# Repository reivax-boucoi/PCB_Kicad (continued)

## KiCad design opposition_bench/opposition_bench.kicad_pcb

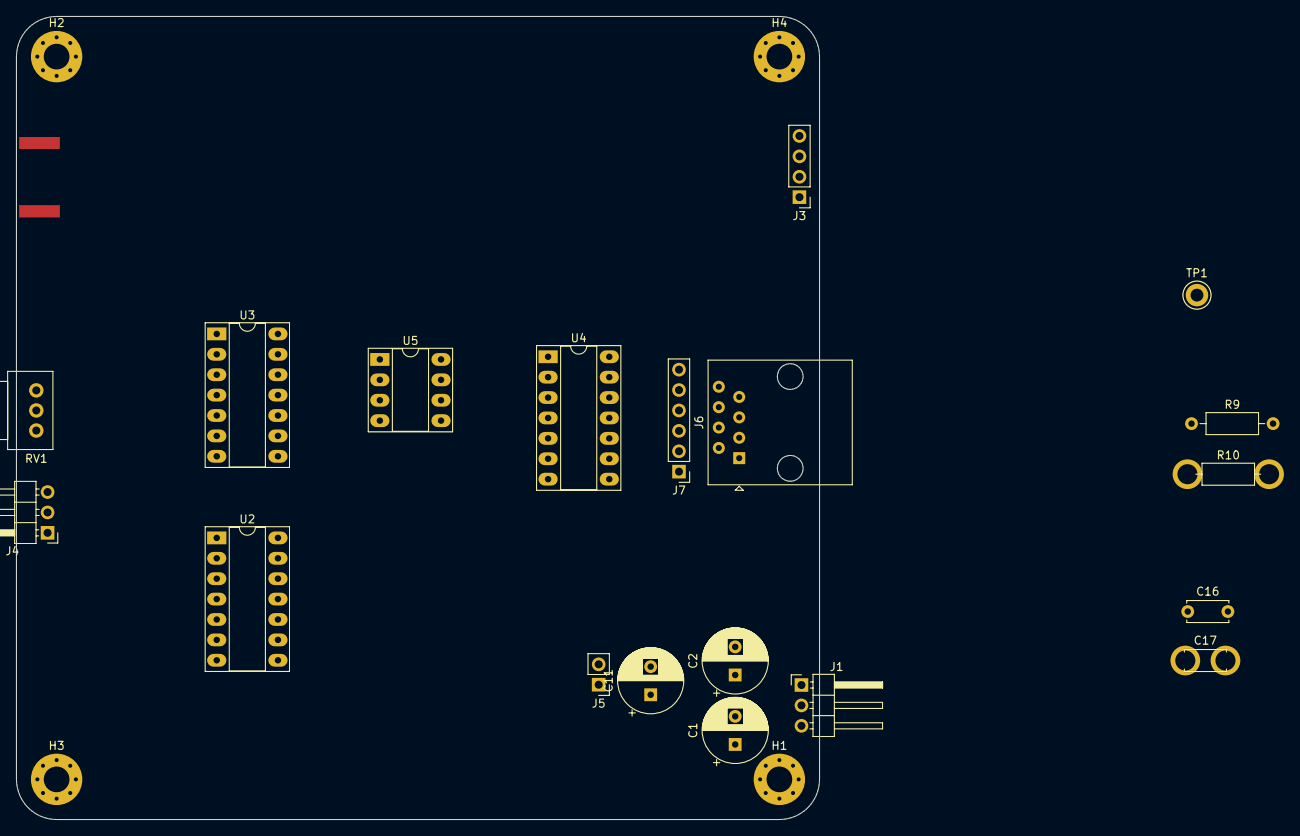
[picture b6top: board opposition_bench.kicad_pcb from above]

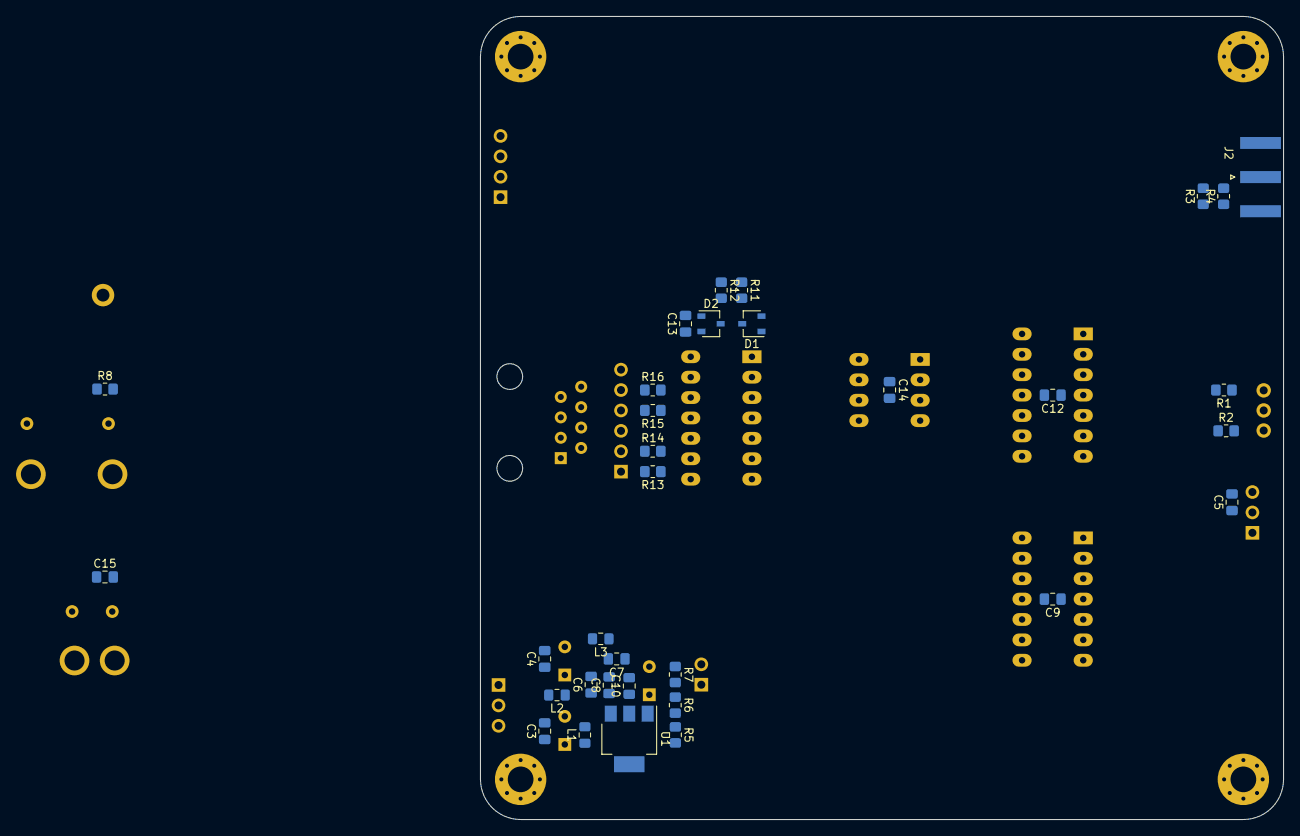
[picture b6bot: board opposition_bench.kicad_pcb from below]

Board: 2 copper layers, 100.0 x 100.0 mm, 56 parts (33 on the bottom side), 26 nets, no tracks yet.

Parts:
C1, C2, C11: 10u; CP_Radial_D8.0mm_P3.50mm
C3, C4, C5, C6, C7, C8, C9, C10, C12, C13, C14, C15: 100n; C_0805_2012Metric_Pad1.18x1.45mm_HandSolder
C16: 100n; C_Disc_D5.0mm_W2.5mm_P5.00mm
C17: 100n; C_Socket_D5.0mm_W2.5mm_P5.00mm
D1, D2: BAT60-04W; SOT-23W
H1, H2, H3, H4: MountingHole_Pad; MountingHole_3.2mm_M3_Pad_Via
J1: PWR_IN; PinHeader_1x03_P2.54mm_Horizontal
J2: BNC_IN; SMA_Amphenol_132289_EdgeMount
J3: Current_sensor; PinHeader_1x04_P2.54mm_Vertical
J4: Vset; PinHeader_1x03_P2.54mm_Horizontal
J5: 5V/3V3; PinHeader_1x02_P2.54mm_Vertical
J6: PWM_OUT_RJ; RJ45_Amphenol_54602-x08_Horizontal
J7: PWM_OUT; PinHeader_1x06_P2.54mm_Vertical
L1, L2, L3: 10u; L_0805_2012Metric_Pad1.15x1.40mm_HandSolder
R1, R2: 4k2; R_0805_2012Metric_Pad1.20x1.40mm_HandSolder
R3, R4: 100; R_0805_2012Metric_Pad1.20x1.40mm_HandSolder
R5: 240; R_0805_2012Metric_Pad1.20x1.40mm_HandSolder
R6: 390; R_0805_2012Metric_Pad1.20x1.40mm_HandSolder
R7: 330; R_0805_2012Metric_Pad1.20x1.40mm_HandSolder
R8, R13, R14, R15, R16: 10; R_0805_2012Metric_Pad1.20x1.40mm_HandSolder
R9: 10; R_Axial_DIN0207_L6.3mm_D2.5mm_P10.16mm_Horizontal
R10: 10; R_Socket_L6.3mm_D2.5mm_P10.16mm_Horizontal
R11, R12: 10k; R_0805_2012Metric_Pad1.20x1.40mm_HandSolder
RV1: 10k; Potentiometer_Alps_RK09Y11_Single_Horizontal
TP1: TestPoint; TestPoint_Keystone_5010-5014_Multipurpose
U1: LM317_SOT-223; SOT-223-3_TabPin2
U2, U3: LM324; DIP-14_W7.62mm_Socket_LongPads
U4: 74HC14; DIP-14_W7.62mm_Socket_LongPads
U5: LM393; DIP-8_W7.62mm_Socket_LongPads

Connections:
+5V: C10.1, C11.1, C13.1, D1.2 (K), D2.2 (K), R5.2, U1.2 (VO), U4.14 (VCC)
+15V: C6.1, C8.1, C9.1, C12.1, C14.1, J3.1, L1.2, R1.2, U1.3 (VI), U2.4 (V+), U3.4 (V+), U5.8 (V+)
-15V: C7.2, C9.2, C12.2, C14.2, J3.2, L3.1, R2.1, U2.11 (V-), U3.11 (V-), U5.4 (V-)
/15V_pre: C1.1, C3.1, J1.3, L1.1
/-15V_pre: C2.2, C4.2, J1.1, L3.2
/GND_pre: C1.2, C2.1, C3.2, C4.1, J1.2, L2.2
/I_setpoint: J2.1 (In), R3.2, R4.2
/PWMHU: R14.1, U4.6
/PWMHU_o: J6.3, J7.2, R14.2
/PWMHV: R16.1, U4.12
/PWMHV_o: J6.7, J7.5, R16.2
/PWMLU: R13.1, U4.4
/PWMLU_o: J6.1, J7.1, R13.2
/PWMLV: R15.1, U4.10
/PWMLV_o: J6.5, J7.4, R15.2
/PWMU_clmp: D1.3 (common), R11.2, U4.1, U4.5
/PWMV_clmp: D2.3 (common), R12.2, U4.9, U4.13
/Reg_fb: R5.1, R6.2, U1.1 (ADJ)
/V_setpoint: C5.1, J4.2
GND: C5.2, C6.2, C7.1, C8.2, C10.2, C11.2, C13.2, D1.1 (A), D2.1 (A), H1.1, H2.1, H3.1, H4.1, J2.2 (Ext), J3.4, J4.3, J5.2, J6.2, J6.4, J6.6, J6.8, J7.3, J7.6, L2.1, R3.1, R4.1, R7.1, U4.7 (GND)
unnamed: J4.1, RV1.2
unnamed: J5.1, R6.1, R7.2
unnamed: R1.1, RV1.1
unnamed: R2.2, RV1.3
unnamed: U4.2, U4.3
unnamed: U4.8, U4.11

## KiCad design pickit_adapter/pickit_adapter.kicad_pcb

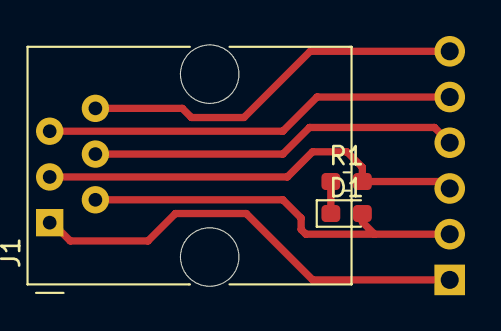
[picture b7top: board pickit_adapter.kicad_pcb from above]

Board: 2 copper layers, 4 parts (1 on the bottom side), 7 nets.

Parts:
D1: LED; LED_0603_1608Metric_Pad1.05x0.95mm_HandSolder
J1: 6P6C_Shielded; RJ12_Amphenol_54601
J2: Conn_PIC_ICSP_ICD; PinHeader_1x06_P2.54mm_Horizontal
R1: 470; R_0603_1608Metric_Pad1.05x0.95mm_HandSolder

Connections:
unnamed: D1.1, R1.1
unnamed: D1.2, J1.2, J2.2
unnamed: J1.1, J2.1
unnamed: J1.3, J2.3, R1.2
unnamed: J1.4, J2.4
unnamed: J1.5, J2.5
unnamed: J1.6, J2.6

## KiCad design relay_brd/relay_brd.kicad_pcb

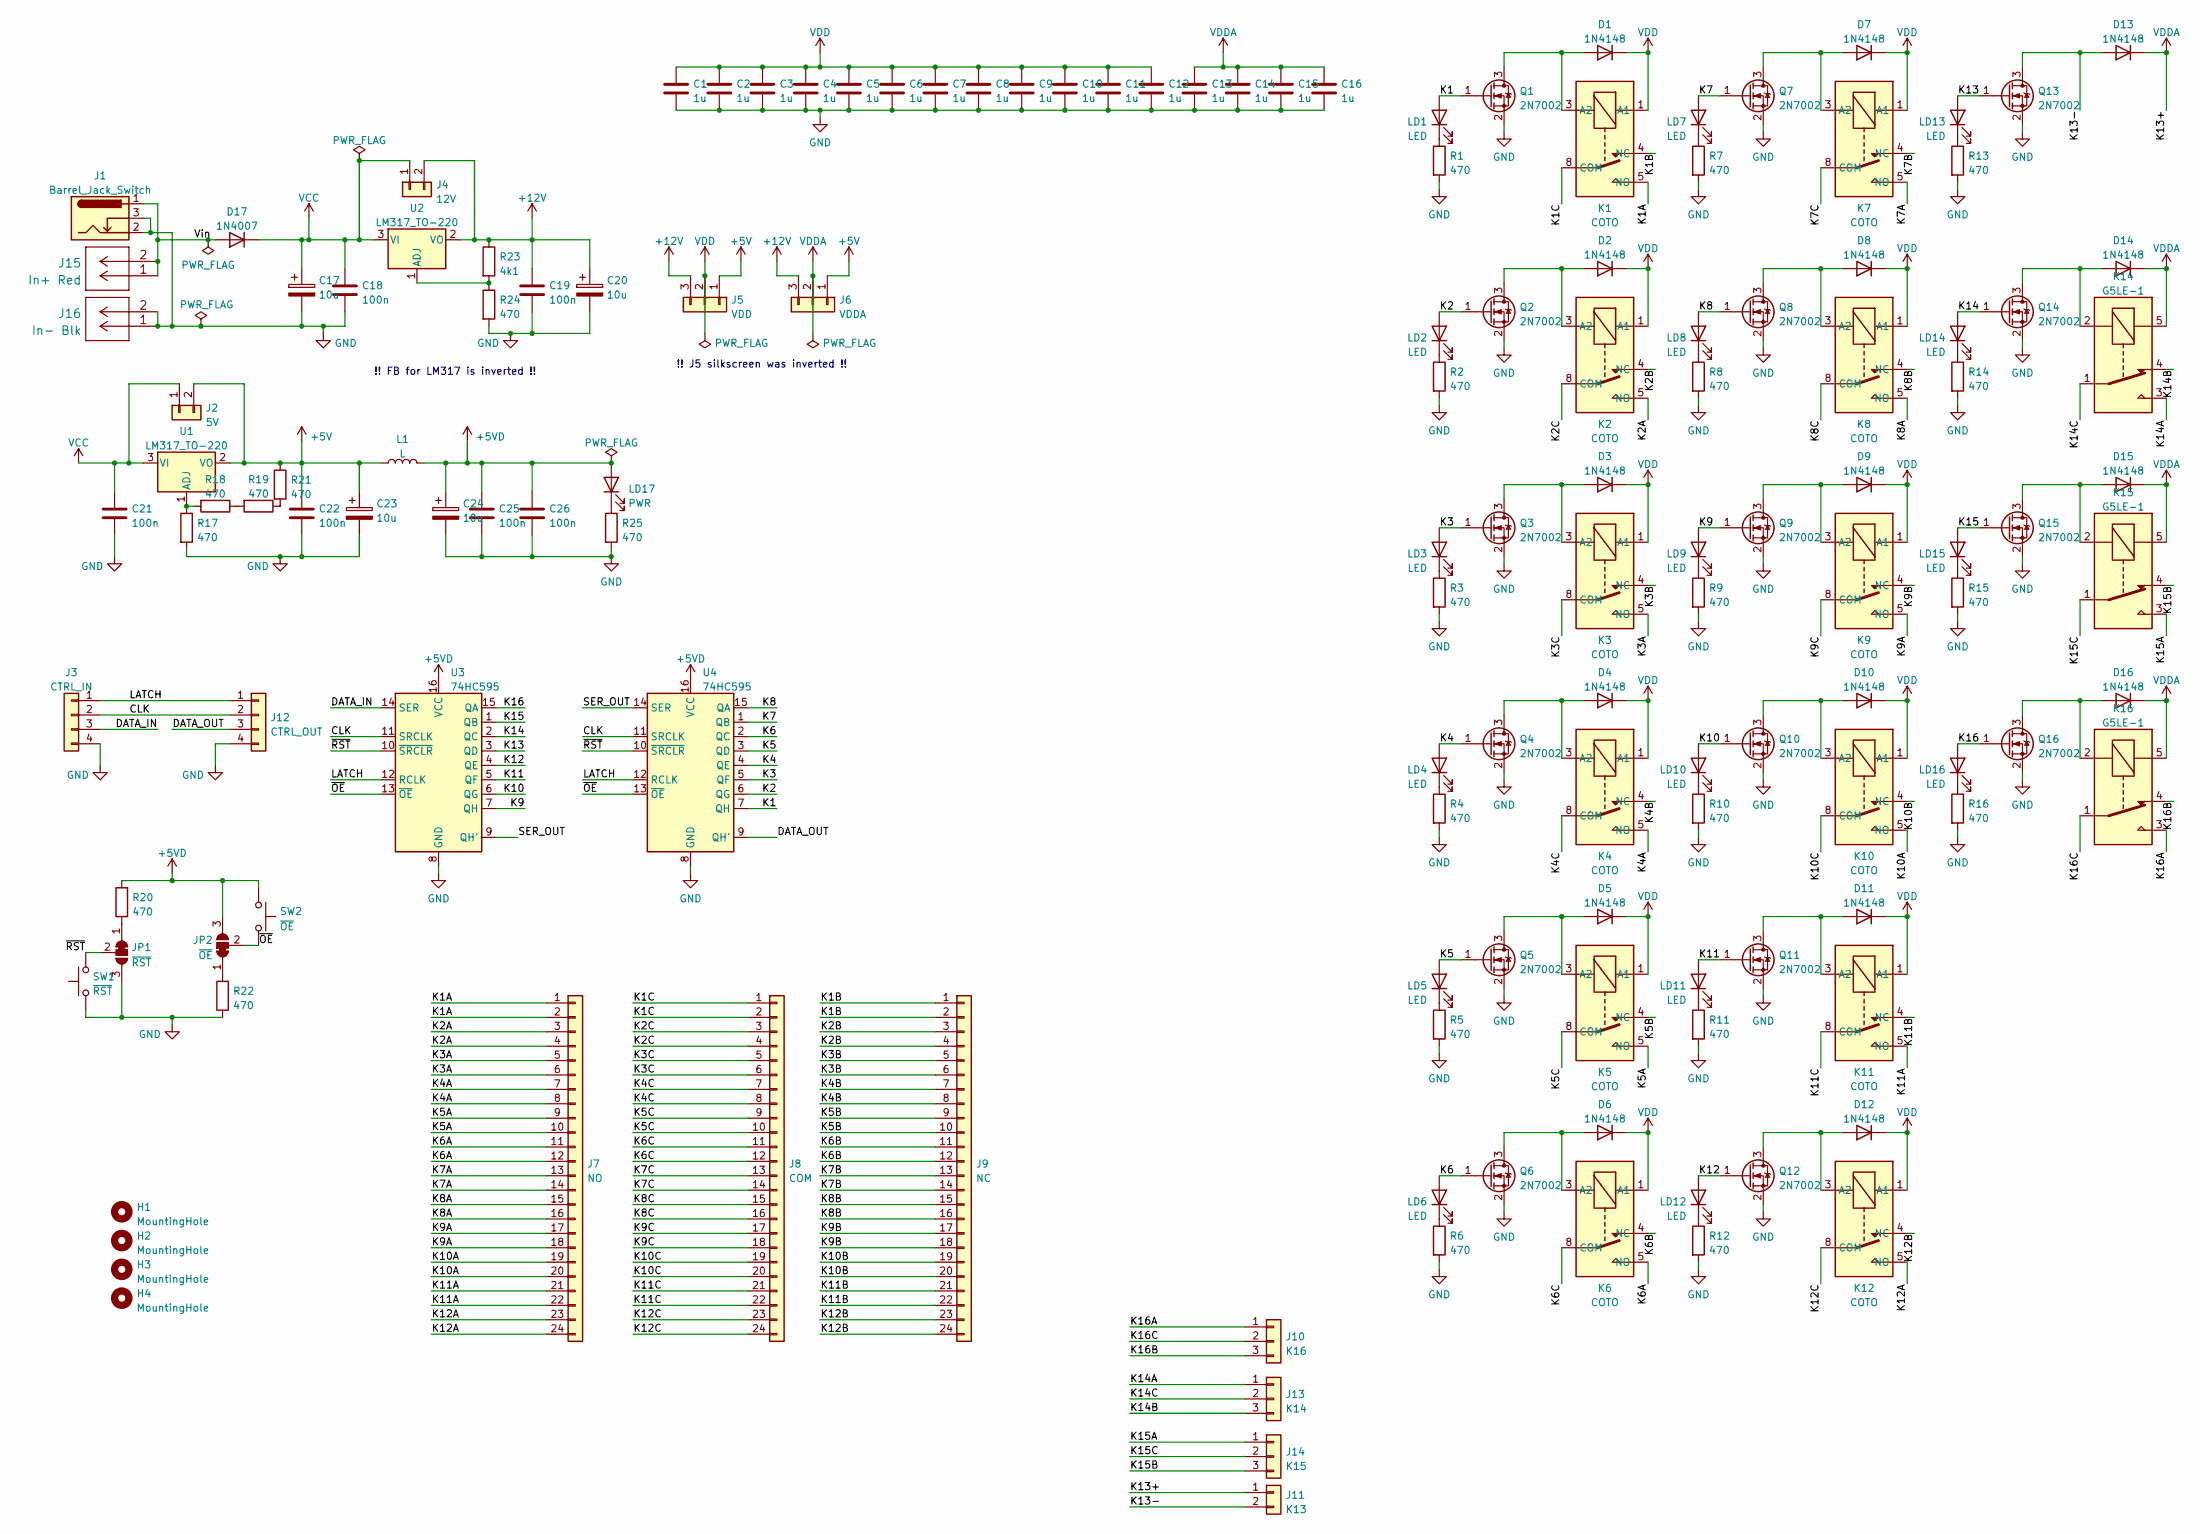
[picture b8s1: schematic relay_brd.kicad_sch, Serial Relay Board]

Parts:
C1, C2, C3, C4, C5, C6, C7, C8, C9, C10, C11, C12, C13, C14, C15, C16: 1u; C_0805_2012Metric
C17, C20, C23, C24: 10u; CP_Radial_D8.0mm_P3.50mm
C18, C19, C21, C22, C25, C26: 100n; C_0603_1608Metric
D1, D2, D3, D4, D5, D6, D7, D8, D9, D10, D11, D12, D13, D14, D15, D16: 1N4148; D_SOD-123
D17: 1N4007; D_DO-41_SOD81_P10.16mm_Horizontal
H1, H2, H3, H4: MountingHole; MountingHole_4.3mm_M4
J1: Barrel_Jack_Switch; BarrelJack_Horizontal
J2: 5V; PinHeader_1x02_P2.54mm_Vertical
J3: CTRL_IN; PinHeader_1x04_P2.54mm_Vertical
J4: 12V; PinHeader_1x02_P2.54mm_Vertical
J5: VDD; PinHeader_1x03_P2.54mm_Vertical
J6: VDDA; PinHeader_1x03_P2.54mm_Vertical
J7: NO; PinHeader_1x24_P2.54mm_Vertical
J8: COM; PinHeader_1x24_P2.54mm_Vertical
J9: NC; PinHeader_1x24_P2.54mm_Vertical
J10: K16; PinHeader_1x03_P2.54mm_Vertical
J11: K13; PinHeader_1x02_P2.54mm_Vertical
J12: CTRL_OUT; PinHeader_1x04_P2.54mm_Vertical
J13: K14; PinHeader_1x03_P2.54mm_Vertical
J14: K15; PinHeader_1x03_P2.54mm_Vertical
J15: In+ Red; 571-0100_Red
J16: In- Blk; 571-0100_Black
JP1: ~{RST}; SolderJumper-3_P1.3mm_Bridged12_RoundedPad1.0x1.5mm_NumberL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
JP2: ~{OE}; SolderJumper-3_P1.3mm_Bridged12_RoundedPad1.0x1.5mm_NumberL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
K1, K2, K3, K4, K5, K6, K7, K8, K9, K10, K11, K12: COTO; COTO-2900
K14, K15, K16: G5LE-1; Relay_SPDT_Omron-G5LE-1
L1: L; L_Axial_L7.0mm_D3.3mm_P12.70mm_Horizontal_Fastron_MICC
LD1, LD2, LD3, LD4, LD5, LD6, LD7, LD8, LD9, LD10, LD11, LD12, LD13, LD14, LD15, LD16: LED; LED_0805_2012Metric
LD17: PWR; LED_0805_2012Metric
Q1, Q2, Q3, Q4, Q5, Q6, Q7, Q8, Q9, Q10, Q11, Q12, Q13, Q14, Q15, Q16: 2N7002; SOT-23
R1, R2, R3, R4, R5, R6, R7, R8, R9, R10, R11, R12, R13, R14, R15, R16, R17, R18, R19, R20, R21, R22, R24, R25: 470; R_0603_1608Metric
R23: 4k1; R_0603_1608Metric
SW1: ~{RST}; SW_PUSH_6mm
SW2: ~{OE}; SW_PUSH_6mm
U1, U2: LM317_TO-220; TO-220-3_Vertical
U3, U4: 74HC595; DIP-16_W7.62mm_Socket_LongPads

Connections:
+5V: C22.1, C23.1, J2.2, J5.1, J6.1, L1.1, R21.1, U1.2 (VO)
+5VD: C24.1, C25.1, C26.1, JP2.3 (B), L1.2, LD17.2 (A), R20.2, SW2.2, U3.16 (VCC), U4.16 (VCC)
+12V: C19.1, C20.1, J4.2, J5.3, J6.3, R23.1, U2.2 (VO)
/CLK: J3.2, J12.2, U3.11 (SRCLK), U4.11 (SRCLK)
/DATA_IN: J3.3, U3.14 (SER)
/DATA_OUT: J12.3, U4.9 (QH')
/K1: LD1.2 (A), Q1.1 (G), U4.7 (QH)
/K1A: J7.1, J7.2, K1.5 (NO)
/K1B: J9.1, J9.2, K1.4 (NC)
/K1C: J8.1, J8.2, K1.8 (COM)
/K2: LD2.2 (A), Q2.1 (G), U4.6 (QG)
/K2A: J7.3, J7.4, K2.5 (NO)
/K2B: J9.3, J9.4, K2.4 (NC)
/K2C: J8.3, J8.4, K2.8 (COM)
/K3: LD3.2 (A), Q3.1 (G), U4.5 (QF)
/K3A: J7.5, J7.6, K3.5 (NO)
/K3B: J9.5, J9.6, K3.4 (NC)
/K3C: J8.5, J8.6, K3.8 (COM)
/K4: LD4.2 (A), Q4.1 (G), U4.4 (QE)
/K4A: J7.7, J7.8, K4.5 (NO)
/K4B: J9.7, J9.8, K4.4 (NC)
/K4C: J8.7, J8.8, K4.8 (COM)
/K5: LD5.2 (A), Q5.1 (G), U4.3 (QD)
/K5A: J7.9, J7.10, K5.5 (NO)
/K5B: J9.9, J9.10, K5.4 (NC)
/K5C: J8.9, J8.10, K5.8 (COM)
/K6: LD6.2 (A), Q6.1 (G), U4.2 (QC)
/K6A: J7.11, J7.12, K6.5 (NO)
/K6B: J9.11, J9.12, K6.4 (NC)
/K6C: J8.11, J8.12, K6.8 (COM)
/K7: LD7.2 (A), Q7.1 (G), U4.1 (QB)
/K7A: J7.13, J7.14, K7.5 (NO)
/K7B: J9.13, J9.14, K7.4 (NC)
/K7C: J8.13, J8.14, K7.8 (COM)
/K8: LD8.2 (A), Q8.1 (G), U4.15 (QA)
/K8A: J7.15, J7.16, K8.5 (NO)
/K8B: J9.15, J9.16, K8.4 (NC)
/K8C: J8.15, J8.16, K8.8 (COM)
/K9: LD9.2 (A), Q9.1 (G), U3.7 (QH)
/K9A: J7.17, J7.18, K9.5 (NO)
/K9B: J9.17, J9.18, K9.4 (NC)
/K9C: J8.17, J8.18, K9.8 (COM)
/K10: LD10.2 (A), Q10.1 (G), U3.6 (QG)
/K10A: J7.19, J7.20, K10.5 (NO)
/K10B: J9.19, J9.20, K10.4 (NC)
/K10C: J8.19, J8.20, K10.8 (COM)
/K11: LD11.2 (A), Q11.1 (G), U3.5 (QF)
/K11A: J7.21, J7.22, K11.5 (NO)
/K11B: J9.21, J9.22, K11.4 (NC)
/K11C: J8.21, J8.22, K11.8 (COM)
/K12: LD12.2 (A), Q12.1 (G), U3.4 (QE)
/K12A: J7.23, J7.24, K12.5 (NO)
/K12B: J9.23, J9.24, K12.4 (NC)
/K12C: J8.23, J8.24, K12.8 (COM)
/K13: LD13.2 (A), Q13.1 (G), U3.3 (QD)
/K13-: D13.2 (A), J11.2, Q13.3 (D)
/K14: LD14.2 (A), Q14.1 (G), U3.2 (QC)
/K14A: J13.1, K14.3
/K14B: J13.3, K14.4
/K14C: J13.2, K14.1
/K15: LD15.2 (A), Q15.1 (G), U3.1 (QB)
/K15A: J14.1, K15.3
/K15B: J14.3, K15.4
/K15C: J14.2, K15.1
/K16: LD16.2 (A), Q16.1 (G), U3.15 (QA)
/K16A: J10.1, K16.3
/K16B: J10.3, K16.4
/K16C: J10.2, K16.1
/LATCH: J3.1, J12.1, U3.12 (RCLK), U4.12 (RCLK)
/SER_OUT: U3.9 (QH'), U4.14 (SER)
/Vin: D17.2 (A), J1.1, J15.1, J15.2
/~OE: JP2.2 (C), SW2.1, U3.13 (~OE), U4.13 (~OE)
/~RST: JP1.2 (C), SW1.2, U3.10 (~SRCLR), U4.10 (~SRCLR)
GND: C1.2, C2.2, C3.2, C4.2, C5.2, C6.2, C7.2, C8.2, C9.2, C10.2, C11.2, C12.2, C13.2, C14.2, C15.2, C16.2, C17.2, C18.2, C19.2, C20.2, C21.2, C22.2, C23.2, C24.2, C25.2, C26.2, J1.2, J1.3, J3.4, J12.4, J16.1, J16.2, JP1.3 (B), Q1.2 (S), Q2.2 (S), Q3.2 (S), Q4.2 (S), Q5.2 (S), Q6.2 (S), Q7.2 (S), Q8.2 (S), Q9.2 (S), Q10.2 (S), Q11.2 (S), Q12.2 (S), Q13.2 (S), Q14.2 (S), Q15.2 (S), Q16.2 (S), R1.2, R2.2, R3.2, R4.2, R5.2, R6.2, R7.2, R8.2, R9.2, R10.2, R11.2, R12.2, R13.2, R14.2, R15.2, R16.2, R17.2, R22.1, R24.2, R25.2, SW1.1, U3.8 (GND), U4.8 (GND)
unnamed: D1.2 (A), K1.3 (A2), Q1.3 (D)
unnamed: D2.2 (A), K2.3 (A2), Q2.3 (D)
unnamed: D3.2 (A), K3.3 (A2), Q3.3 (D)
unnamed: D4.2 (A), K4.3 (A2), Q4.3 (D)
unnamed: D5.2 (A), K5.3 (A2), Q5.3 (D)
unnamed: D6.2 (A), K6.3 (A2), Q6.3 (D)
unnamed: D7.2 (A), K7.3 (A2), Q7.3 (D)
unnamed: D8.2 (A), K8.3 (A2), Q8.3 (D)
unnamed: D9.2 (A), K9.3 (A2), Q9.3 (D)
unnamed: D10.2 (A), K10.3 (A2), Q10.3 (D)
unnamed: D11.2 (A), K11.3 (A2), Q11.3 (D)
unnamed: D12.2 (A), K12.3 (A2), Q12.3 (D)
unnamed: D14.2 (A), K14.2, Q14.3 (D)
unnamed: D15.2 (A), K15.2, Q15.3 (D)
unnamed: D16.2 (A), K16.2, Q16.3 (D)
unnamed: JP1.1 (A), R20.1
unnamed: JP2.1 (A), R22.2
unnamed: LD1.1 (K), R1.1
unnamed: LD2.1 (K), R2.1
unnamed: LD3.1 (K), R3.1
unnamed: LD4.1 (K), R4.1
unnamed: LD5.1 (K), R5.1
unnamed: LD6.1 (K), R6.1
unnamed: LD7.1 (K), R7.1
unnamed: LD8.1 (K), R8.1
unnamed: LD9.1 (K), R9.1
unnamed: LD10.1 (K), R10.1
unnamed: LD11.1 (K), R11.1
unnamed: LD12.1 (K), R12.1
unnamed: LD13.1 (K), R13.1
unnamed: LD14.1 (K), R14.1
unnamed: LD15.1 (K), R15.1
unnamed: LD16.1 (K), R16.1
unnamed: LD17.1 (K), R25.1
unnamed: R17.1, R18.2, U1.1 (ADJ)
unnamed: R18.1, R19.2
unnamed: R19.1, R21.2
unnamed: R23.2, R24.1, U2.1 (ADJ)
VCC: C17.1, C18.1, C21.1, D17.1 (K), J2.1, J4.1, U1.3 (VI), U2.3 (VI)
VDD: C1.1, C2.1, C3.1, C4.1, C5.1, C6.1, C7.1, C8.1, C9.1, C10.1, C11.1, C12.1, D1.1 (K), D2.1 (K), D3.1 (K), D4.1 (K), D5.1 (K), D6.1 (K), D7.1 (K), D8.1 (K), D9.1 (K), D10.1 (K), D11.1 (K), D12.1 (K), J5.2, K1.1 (A1), K2.1 (A1), K3.1 (A1), K4.1 (A1), K5.1 (A1), K6.1 (A1), K7.1 (A1), K8.1 (A1), K9.1 (A1), K10.1 (A1), K11.1 (A1), K12.1 (A1)
VDDA: C13.1, C14.1, C15.1, C16.1, D13.1 (K), D14.1 (K), D15.1 (K), D16.1 (K), J6.2, J11.1, K14.5, K15.5, K16.5

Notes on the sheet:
!! J5 silkscreen was inverted !!
!! FB for LM317 is inverted !!

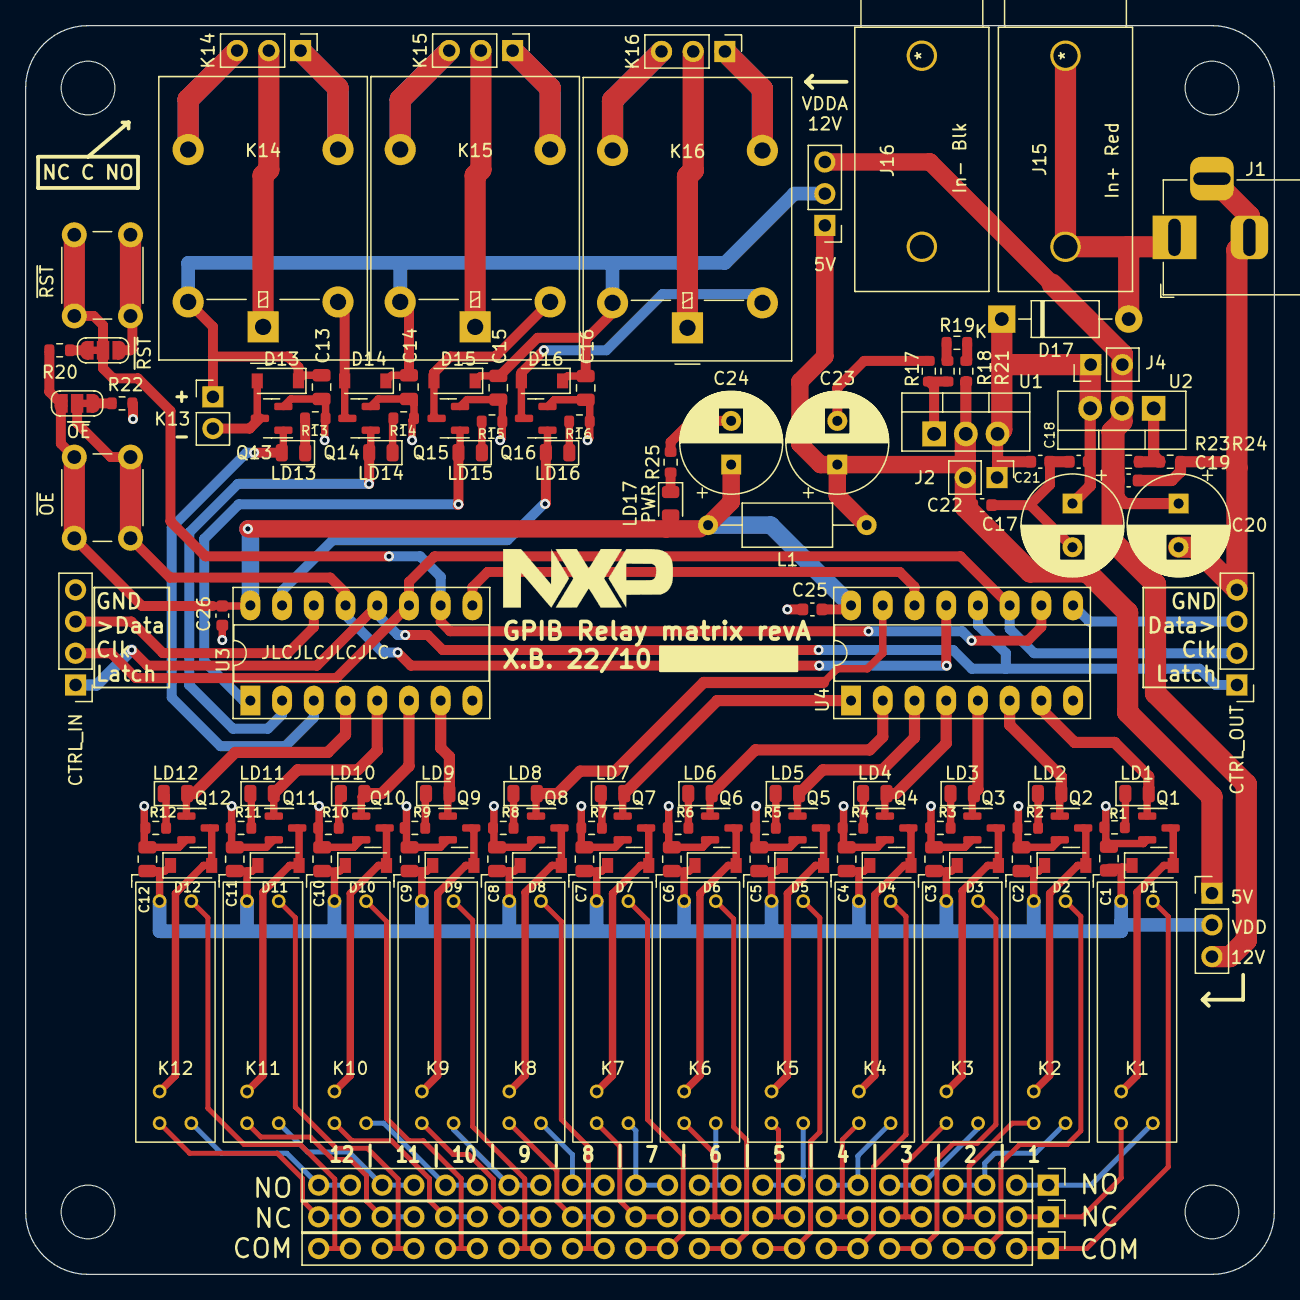
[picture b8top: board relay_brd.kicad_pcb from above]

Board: 2 copper layers, 100.0 x 100.0 mm, 145 parts (0 on the bottom side), 115 nets.

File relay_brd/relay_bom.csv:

Designator	Value	Footprint	JLCPCB Part #
C1, C3, C4, C7, C8, C10	100n	Capacitor_SMD:C_0603_1608Metric	
C2, C5, C6, C9	10u	Capacitor_THT:CP_Radial_D8.0mm_P3.50mm	
D1, D2, D3, D4, D5, D6, D7, D8, D9, D10, D11, D12, D13, D14, D15, D16	1N4148	Diode_SMD:D_SOD-123	
D17	1N4007	Diode_THT:D_DO-41_SOD81_P10.16mm_Horizontal	
H1, H2, H3, H4	MountingHole	MountingHole:MountingHole_4.3mm_M4	
J1	PWR	Connector_PinHeader_2.54mm:PinHeader_1x02_P2.54mm_Vertical	
J2	5V	Connector_PinHeader_2.54mm:PinHeader_1x02_P2.54mm_Vertical	
J3	CTRL	Connector_PinSocket_2.54mm:PinSocket_1x04_P2.54mm_Vertical	
J4	12V	Connector_PinHeader_2.54mm:PinHeader_1x02_P2.54mm_Vertical	
J5	VDD	Connector_PinSocket_2.54mm:PinSocket_1x03_P2.54mm_Vertical	
J6	VDDA	Connector_PinSocket_2.54mm:PinSocket_1x03_P2.54mm_Vertical	
J7	OUT	Connector_PinSocket_2.54mm:PinSocket_2x16_P2.54mm_Vertical	
JP1	~{RST}	Jumper:SolderJumper-3_P1.3mm_Bridged12_RoundedPad1.0x1.5mm_NumberLabels	
JP2	~{OE}	Jumper:SolderJumper-3_P1.3mm_Bridged12_RoundedPad1.0x1.5mm_NumberLabels	
K1, K2, K3, K4, K5, K6, K7, K8, K9, K10, K11, K12, K13, K14, K15, K16	COTO	Relay_THT:Relay_StandexMeder_DIP_LowProfile	
L1	L	Inductor_THT:L_Axial_L7.0mm_D3.3mm_P12.70mm_Horizontal_Fastron_MICC	
LD1, LD2, LD3, LD4, LD5, LD6, LD7, LD8, LD9, LD10, LD11, LD12, LD13, LD14, LD15, LD16, LD17	LED	LED_SMD:LED_0805_2012Metric	
Q1, Q2, Q3, Q4, Q5, Q6, Q7, Q8, Q9, Q10, Q11, Q12, Q13, Q14, Q15, Q16	2N7002	Package_TO_SOT_SMD:SOT-23	
R1, R2, R3, R4, R5, R6, R7, R8, R9, R10, R11, R12, R13, R14, R15, R16, R17, R18, R19, R20, R21, R22, R24, R25	470	Resistor_SMD:R_0603_1608Metric	
R23	4k1	Resistor_SMD:R_0603_1608Metric	
SW1	~{RST}	Button_Switch_THT:SW_PUSH_6mm	
SW2	~{OE}	Button_Switch_THT:SW_PUSH_6mm	
TP1	SER_OUT	TestPoint:TestPoint_Keystone_5010-5014_Multipurpose	
U1, U2	LM317_TO-220	Package_TO_SOT_THT:TO-220-3_Vertical	
U3, U4	74HC595	Package_DIP:DIP-16_W7.62mm_Socket_LongPads
